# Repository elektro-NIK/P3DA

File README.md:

# P3DA

This is RGB controller based on Arduino board.

Features:
- 6 RGB chanels (18 mono-chanels)
- common anode or cathode
- light, effect, sound, external backlight modes
- white balance, gamma correction

Install:
- `pip3 install PyQt5` and `python3 setup.py install` for use in your system
- or `pip3 install -e .` for install all necessary modules

Using: 
- `./software/main.py` for starting
- `/software/test.py` test rainbow ilumination on 0 channel

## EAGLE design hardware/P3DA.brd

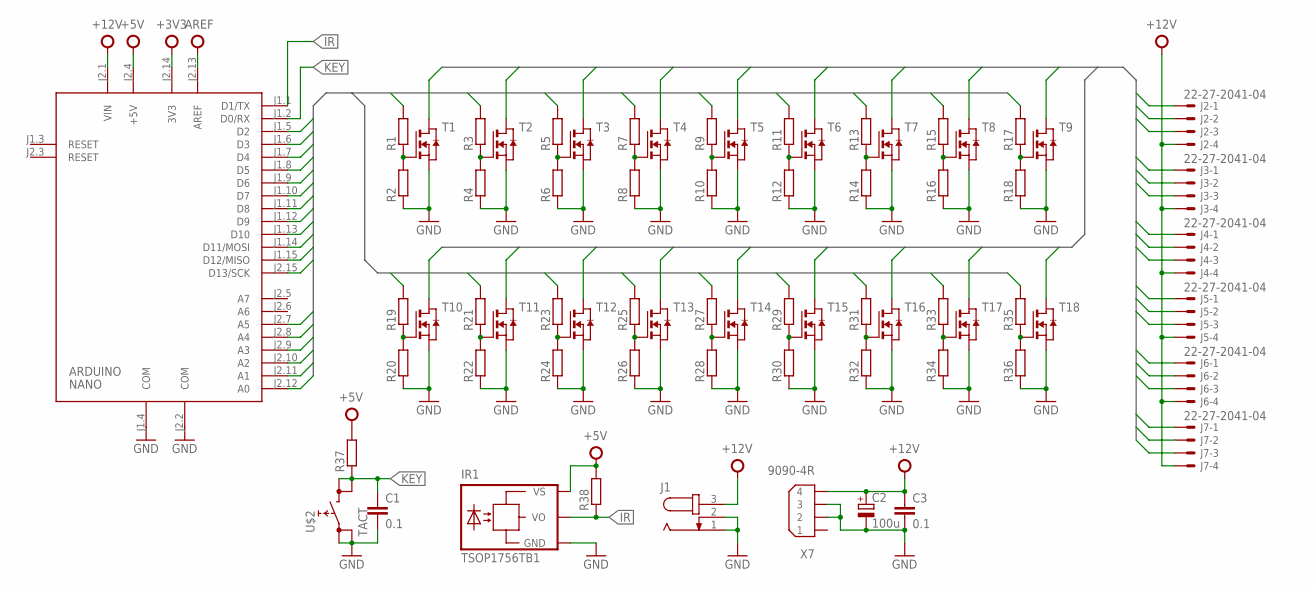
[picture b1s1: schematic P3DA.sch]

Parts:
ARDUINO: NANO; ARDUINO_NANO2
C1: 0.1; C0805
C2: 100u; E5-13
C3: 0.1; C1206
IR1: TSOP1756TB1; TSOP17_TB1
J1: JACK-PLUG1; SPC4078
J2, J3, J4, J5, J6, J7: 22-27-2041-04; 6410-04
R1, R2, R3, R4, R5, R6, R7, R8, R9, R10, R11, R12, R13, R14, R15, R16, R17, R18, R19, R20, R21, R22, R23, R24, R25, R26, R27, R28, R29, R30, R31, R32, R33, R34, R35, R36, R37, R38: R-EU_R0805; R0805
T1, T2, T3, T4, T5, T6, T7, T8, T9, T10, T11, T12, T13, T14, T15, T16, T17, T18: NMOSSOT23; SOT-23
U$2: TACT; TL1105
X7: 9090-4R

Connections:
+3V3: ARDUINO.J2.14 (3V3)
+5V: ARDUINO.J2.4 (+5V), IR1.VS, R37.2, R38.2
+12V: ARDUINO.J2.1 (VIN), C2.+, C3.1, J1.3, J2.4, J3.4, J4.4, J5.4, J6.4, J7.4, X7.4
AREF: ARDUINO.J2.13 (AREF)
B1: J2.1, T3.1 (D)
B2: J3.1, T6.1 (D)
B3: J4.1, T9.1 (D)
B4: J5.1, T12.1 (D)
B5: J6.1, T15.1 (D)
B6: J7.1, T18.1 (D)
B_IN1: ARDUINO.J1.5 (D2), R5.2
B_IN2: ARDUINO.J1.8 (D5), R11.2
B_IN3: ARDUINO.J1.11 (D8), R17.2
B_IN4: ARDUINO.J2.9 (A3), R23.2
B_IN5: ARDUINO.J2.12 (A0), R29.2
B_IN6: ARDUINO.J1.15 (D12/MISO), R35.2
G1: J2.3, T2.1 (D)
G2: J3.3, T5.1 (D)
G3: J4.3, T8.1 (D)
G4: J5.3, T11.1 (D)
G5: J6.3, T14.1 (D)
G6: J7.3, T17.1 (D)
GND: ARDUINO.J1.4 (COM), ARDUINO.J2.2 (COM), C1.2, C2.-, C3.2, IR1.GND, J1.1, J1.2, R2.1, R4.1, R6.1, R8.1, R10.1, R12.1, R14.1, R16.1, R18.1, R20.1, R22.1, R24.1, R26.1, R28.1, R30.1, R32.1, R34.1, R36.1, T1.2 (S), T2.2 (S), T3.2 (S), T4.2 (S), T5.2 (S), T6.2 (S), T7.2 (S), T8.2 (S), T9.2 (S), T10.2 (S), T11.2 (S), T12.2 (S), T13.2 (S), T14.2 (S), T15.2 (S), T16.2 (S), T17.2 (S), T18.2 (S), U$2.1 (0), U$2.3 (0), X7.2, X7.3
G_IN1: ARDUINO.J1.7 (D4), R3.2
G_IN2: ARDUINO.J1.10 (D7), R9.2
G_IN3: ARDUINO.J1.13 (D10), R15.2
G_IN4: ARDUINO.J2.7 (A5), R21.2
G_IN5: ARDUINO.J2.10 (A2), R27.2
G_IN6: ARDUINO.J2.15 (D13/SCK), R33.2
IR: ARDUINO.J1.1 (D1/TX), IR1.VO, R38.1
KEY: ARDUINO.J1.2 (D0/RX), C1.1, R37.1, U$2.2 (1), U$2.4 (1)
unnamed: R7.1, R8.2, T4.3 (G)
unnamed: R9.1, R10.2, T5.3 (G)
unnamed: R5.1, R6.2, T3.3 (G)
unnamed: R11.1, R12.2, T6.3 (G)
unnamed: R13.1, R14.2, T7.3 (G)
unnamed: R15.1, R16.2, T8.3 (G)
unnamed: R17.1, R18.2, T9.3 (G)
unnamed: R19.1, R20.2, T10.3 (G)
unnamed: R21.1, R22.2, T11.3 (G)
unnamed: R23.1, R24.2, T12.3 (G)
unnamed: R25.1, R26.2, T13.3 (G)
unnamed: R27.1, R28.2, T14.3 (G)
unnamed: R29.1, R30.2, T15.3 (G)
unnamed: R31.1, R32.2, T16.3 (G)
unnamed: R33.1, R34.2, T17.3 (G)
unnamed: R35.1, R36.2, T18.3 (G)
unnamed: R1.1, R2.2, T1.3 (G)
unnamed: R3.1, R4.2, T2.3 (G)
R1: J2.2, T1.1 (D)
R2: J3.2, T4.1 (D)
R3: J4.2, T7.1 (D)
R4: J5.2, T10.1 (D)
R5: J6.2, T13.1 (D)
R6: J7.2, T16.1 (D)
R_IN1: ARDUINO.J1.6 (D3), R1.2
R_IN2: ARDUINO.J1.9 (D6), R7.2
R_IN3: ARDUINO.J1.12 (D9), R13.2
R_IN4: ARDUINO.J2.8 (A4), R19.2
R_IN5: ARDUINO.J2.11 (A1), R25.2
R_IN6: ARDUINO.J1.14 (D11/MOSI), R31.2

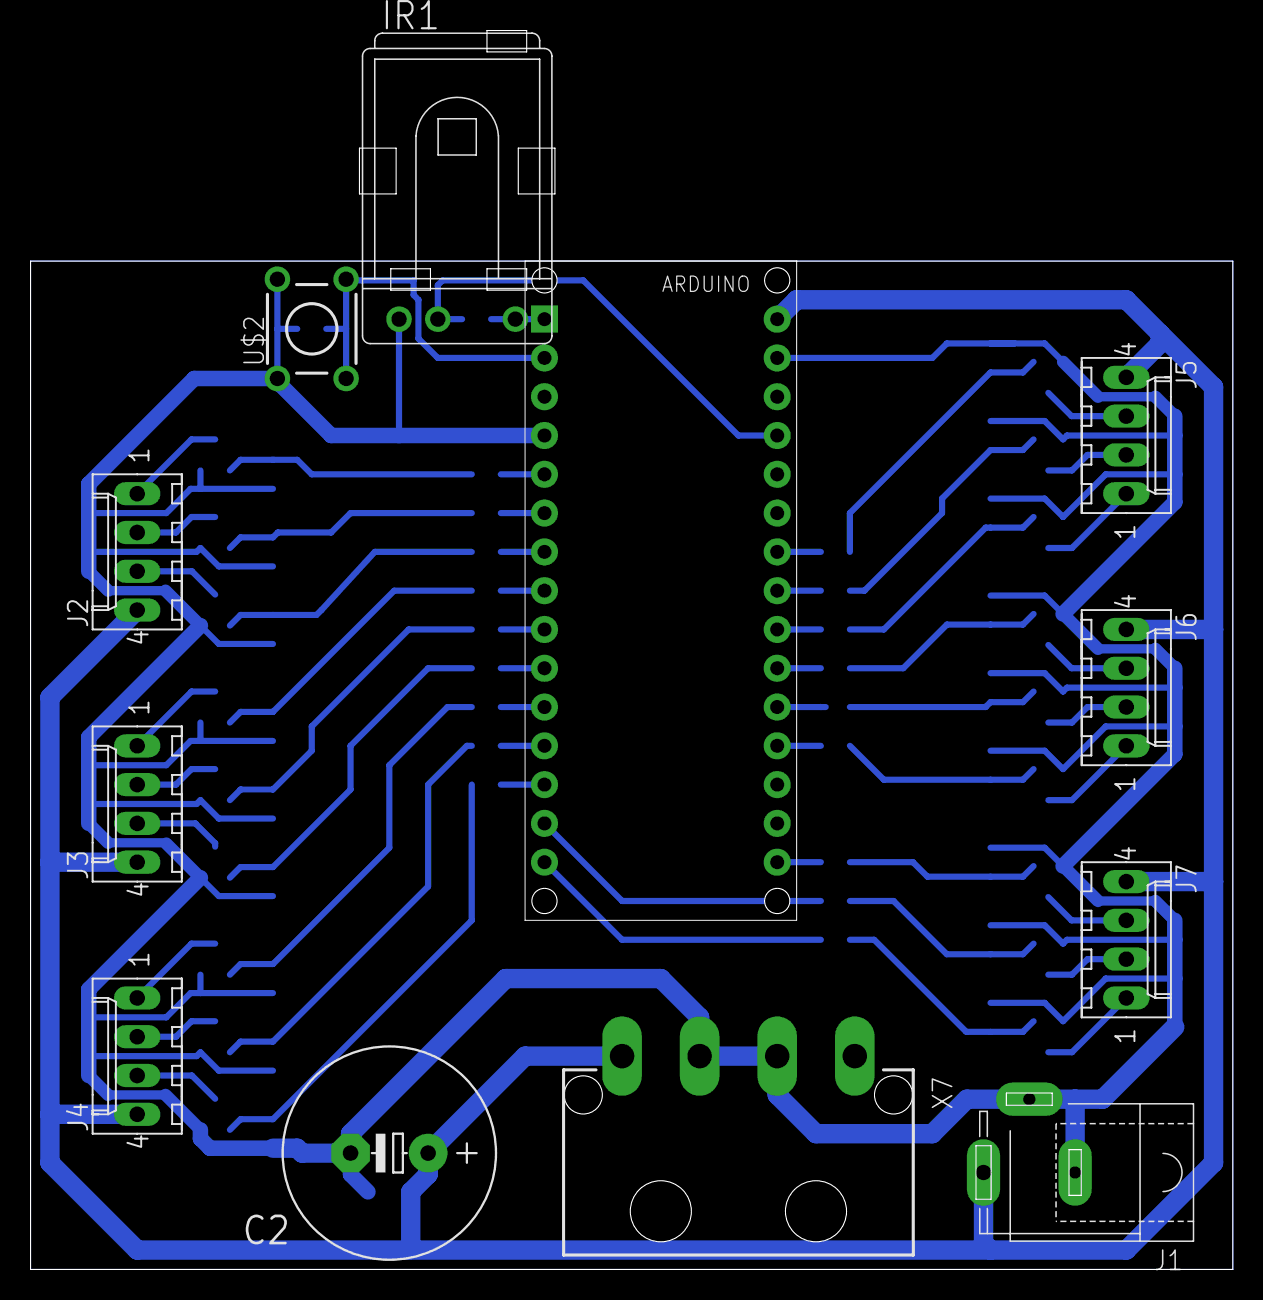
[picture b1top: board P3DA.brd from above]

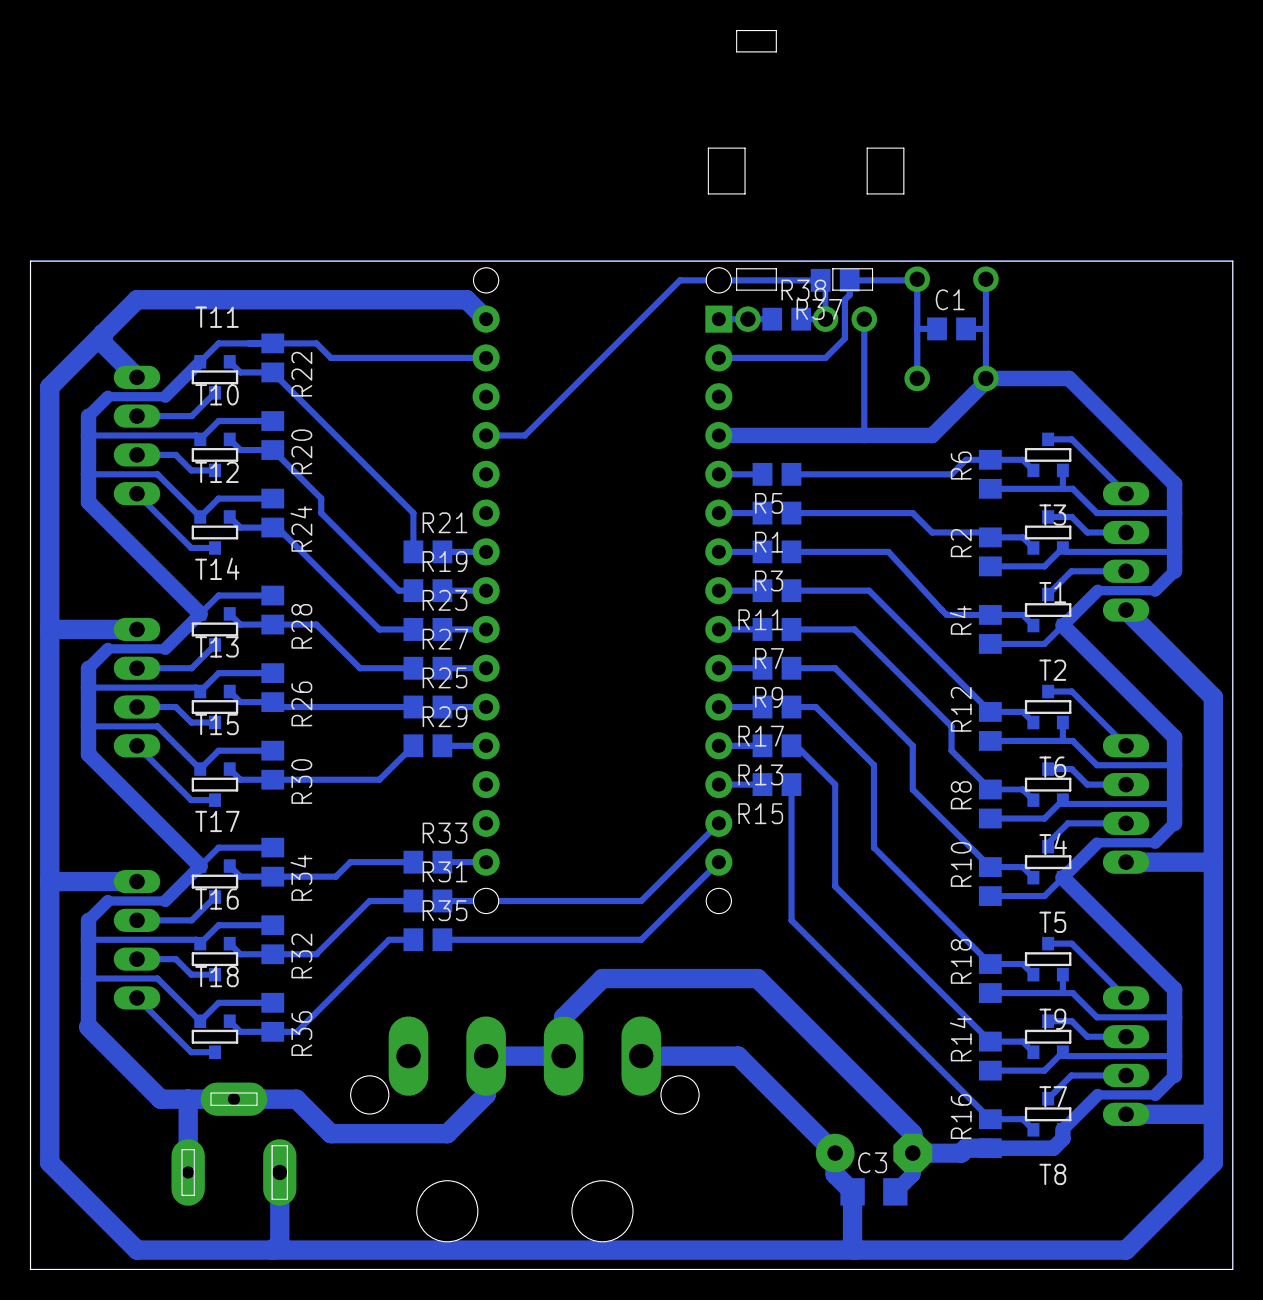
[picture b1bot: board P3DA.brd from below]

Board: 2 copper layers, 78.7 x 81.1 mm, 70 parts (58 on the bottom side), 59 nets.

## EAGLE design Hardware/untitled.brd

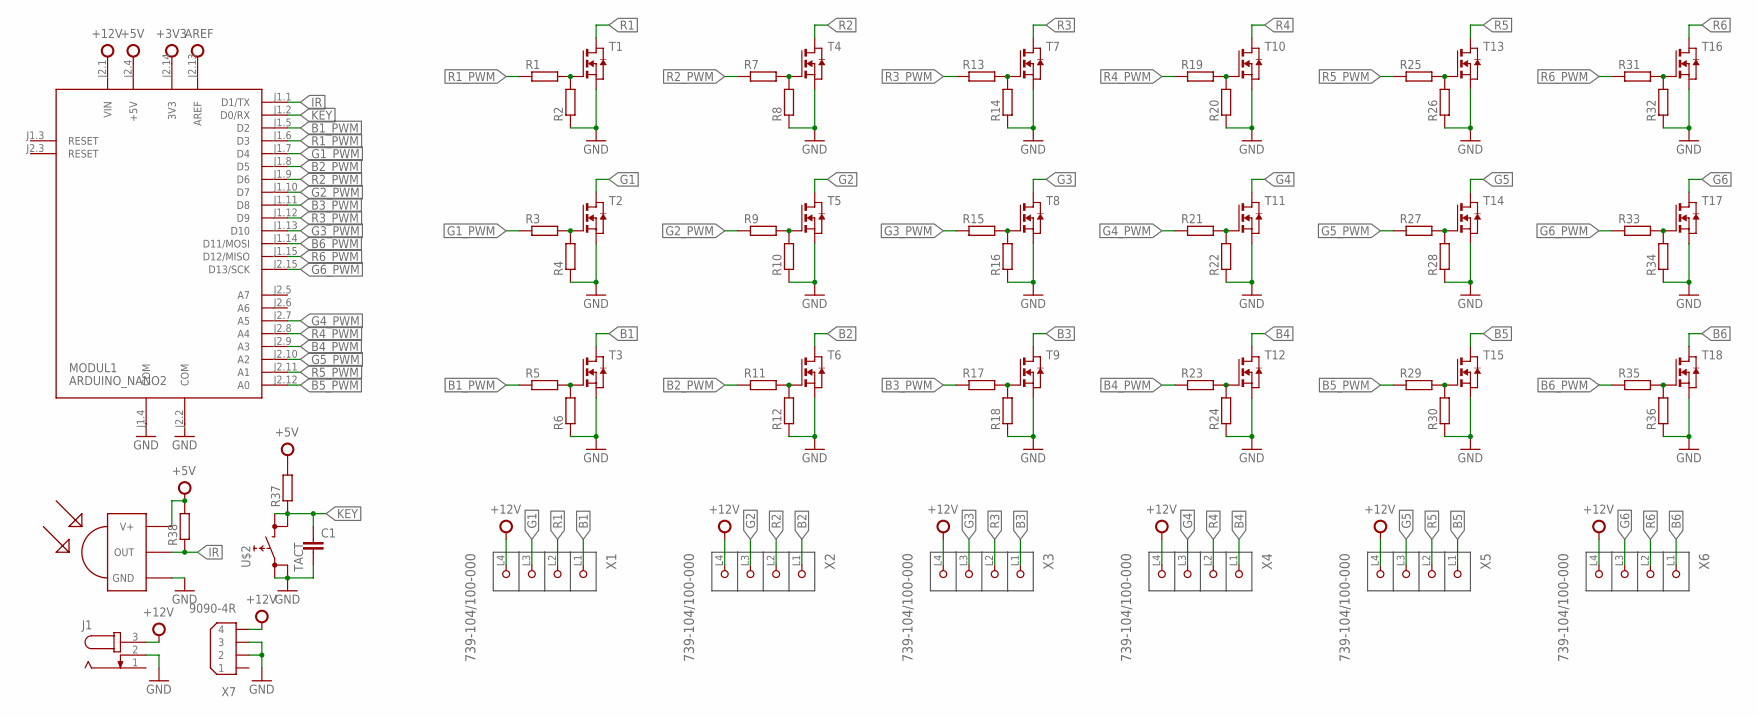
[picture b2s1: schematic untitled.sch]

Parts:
C1: C-EUC0805; C0805
J1: JACK-PLUG1; SPC4078
MODUL1: ARDUINO_NANO2
R1, R2, R3, R4, R5, R6, R7, R8, R9, R10, R11, R12, R13, R14, R15, R16, R17, R18, R19, R20, R21, R22, R23, R24, R25, R26, R27, R28, R29, R30, R31, R32, R33, R34, R35, R36, R37, R38: R-EU_R0805; R0805
T1, T2, T3, T4, T5, T6, T7, T8, T9, T10, T11, T12, T13, T14, T15, T16, T17, T18: NMOSSOT23; SOT-23
U$1: TSOP1738; TSOP17XX
U$2: TACT; TL1105
X1, X2, X3, X4, X5, X6: 739-104/100-000; P-739-104/100-000
X7: 9090-4R

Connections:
+3V3: MODUL1.J2.14 (3V3)
+5V: MODUL1.J2.4 (+5V), R37.2, R38.2, U$1.V+
+12V: J1.3, MODUL1.J2.1 (VIN), X1.L4 (P4), X2.L4 (P4), X3.L4 (P4), X4.L4 (P4), X5.L4 (P4), X6.L4 (P4), X7.4
AREF: MODUL1.J2.13 (AREF)
B1: T3.1 (D), X1.L1 (P1)
B1_PWM: MODUL1.J1.5 (D2), R5.1
B2: T6.1 (D), X2.L1 (P1)
B2_PWM: MODUL1.J1.8 (D5), R11.1
B3: T9.1 (D), X3.L1 (P1)
B3_PWM: MODUL1.J1.11 (D8), R17.1
B4: T12.1 (D), X4.L1 (P1)
B4_PWM: MODUL1.J2.9 (A3), R23.1
B5: T15.1 (D), X5.L1 (P1)
B5_PWM: MODUL1.J2.12 (A0), R29.1
B6: T18.1 (D), X6.L1 (P1)
B6_PWM: MODUL1.J1.14 (D11/MOSI), R35.1
G1: T2.1 (D), X1.L3 (P3)
G1_PWM: MODUL1.J1.7 (D4), R3.1
G2: T5.1 (D), X2.L3 (P3)
G2_PWM: MODUL1.J1.10 (D7), R9.1
G3: T8.1 (D), X3.L3 (P3)
G3_PWM: MODUL1.J1.13 (D10), R15.1
G4: T11.1 (D), X4.L3 (P3)
G4_PWM: MODUL1.J2.7 (A5), R21.1
G5: T14.1 (D), X5.L3 (P3)
G5_PWM: MODUL1.J2.10 (A2), R27.1
G6: T17.1 (D), X6.L3 (P3)
G6_PWM: MODUL1.J2.15 (D13/SCK), R33.1
GND: C1.2, J1.2, MODUL1.J1.4 (COM), MODUL1.J2.2 (COM), R2.1, R4.1, R6.1, R8.1, R10.1, R12.1, R14.1, R16.1, R18.1, R20.1, R22.1, R24.1, R26.1, R28.1, R30.1, R32.1, R34.1, R36.1, T1.2 (S), T2.2 (S), T3.2 (S), T4.2 (S), T5.2 (S), T6.2 (S), T7.2 (S), T8.2 (S), T9.2 (S), T10.2 (S), T11.2 (S), T12.2 (S), T13.2 (S), T14.2 (S), T15.2 (S), T16.2 (S), T17.2 (S), T18.2 (S), U$1.GND, U$2.1 (0), U$2.3 (0), X7.2, X7.3
IR: MODUL1.J1.1 (D1/TX), R38.1, U$1.OUT
KEY: C1.1, MODUL1.J1.2 (D0/RX), R37.1, U$2.2 (1), U$2.4 (1)
unnamed: R1.2, R2.2, T1.3 (G)
unnamed: R7.2, R8.2, T4.3 (G)
unnamed: R9.2, R10.2, T5.3 (G)
unnamed: R3.2, R4.2, T2.3 (G)
unnamed: R5.2, R6.2, T3.3 (G)
unnamed: R11.2, R12.2, T6.3 (G)
unnamed: R13.2, R14.2, T7.3 (G)
unnamed: R15.2, R16.2, T8.3 (G)
unnamed: R17.2, R18.2, T9.3 (G)
unnamed: R19.2, R20.2, T10.3 (G)
unnamed: R21.2, R22.2, T11.3 (G)
unnamed: R23.2, R24.2, T12.3 (G)
unnamed: R25.2, R26.2, T13.3 (G)
unnamed: R27.2, R28.2, T14.3 (G)
unnamed: R29.2, R30.2, T15.3 (G)
unnamed: R31.2, R32.2, T16.3 (G)
unnamed: R33.2, R34.2, T17.3 (G)
unnamed: R35.2, R36.2, T18.3 (G)
R1: T1.1 (D), X1.L2 (P2)
R1_PWM: MODUL1.J1.6 (D3), R1.1
R2: T4.1 (D), X2.L2 (P2)
R2_PWM: MODUL1.J1.9 (D6), R7.1
R3: T7.1 (D), X3.L2 (P2)
R3_PWM: MODUL1.J1.12 (D9), R13.1
R4: T10.1 (D), X4.L2 (P2)
R4_PWM: MODUL1.J2.8 (A4), R19.1
R5: T13.1 (D), X5.L2 (P2)
R5_PWM: MODUL1.J2.11 (A1), R25.1
R6: T16.1 (D), X6.L2 (P2)
R6_PWM: MODUL1.J1.15 (D12/MISO), R31.1

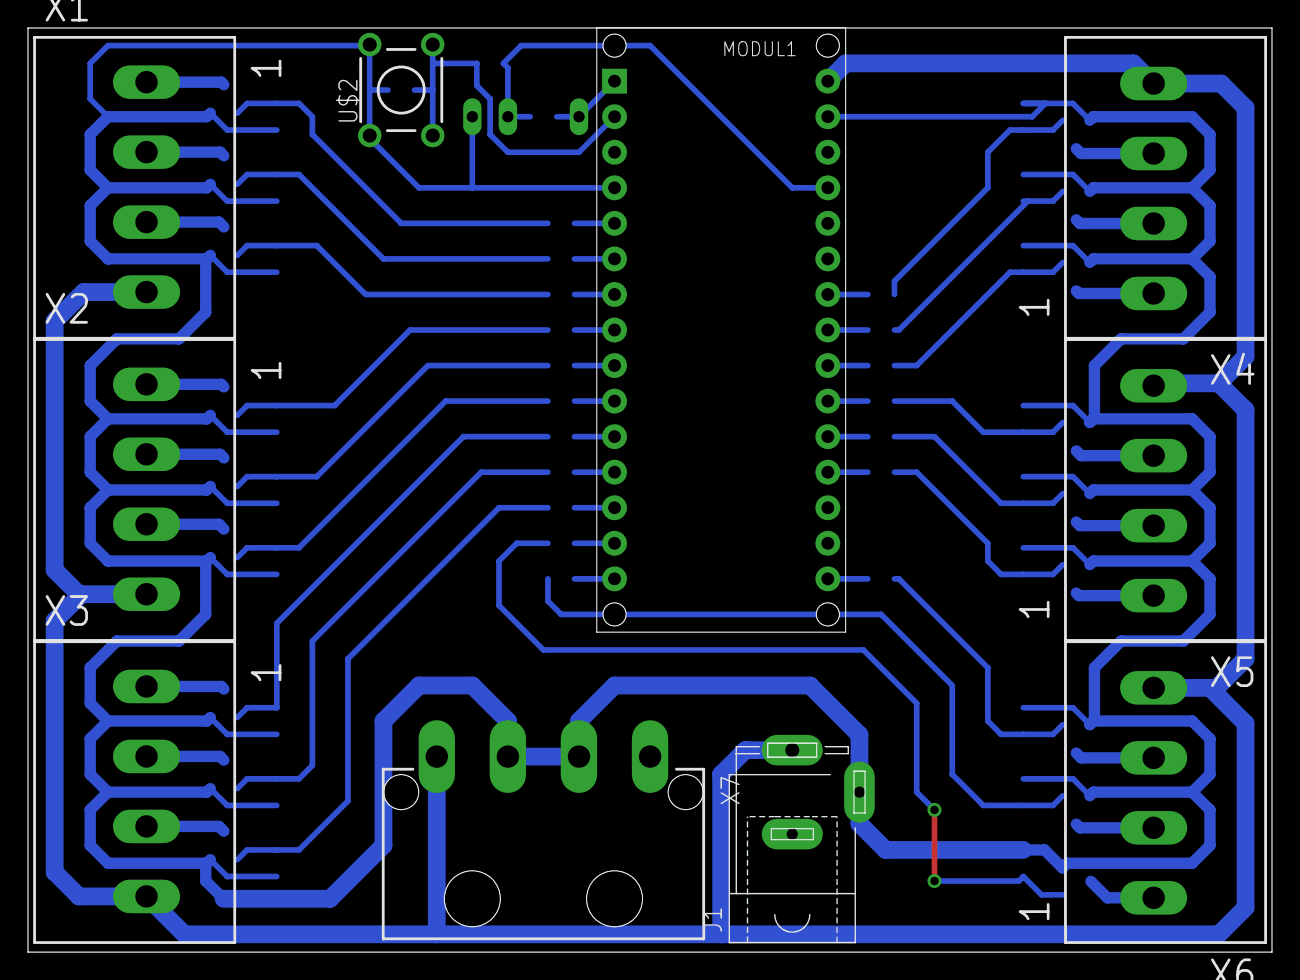
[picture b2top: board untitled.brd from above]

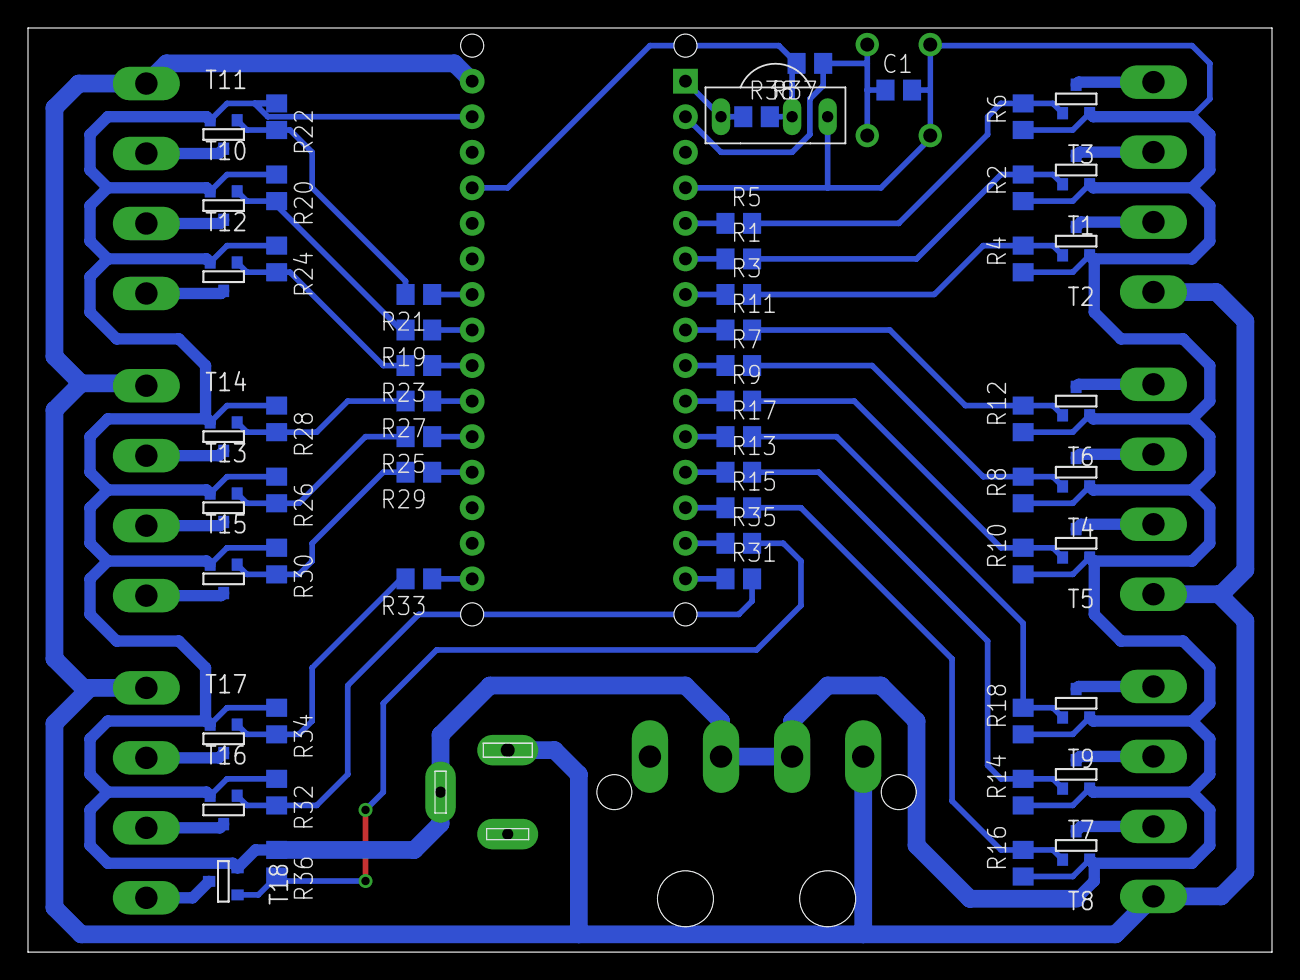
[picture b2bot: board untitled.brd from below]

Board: 2 copper layers, 88.9 x 66.0 mm, 68 parts (58 on the bottom side), 59 nets.

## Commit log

2016-09-03 Add hex-file, bugfix test.c
2016-09-03 Bugfix test.c
2016-09-03 Add Makefile
2016-09-03 Relocate all files
2016-09-04 Update all files
2016-09-04 Added Firmware directory
2016-09-04 Update: main.c. 0 level fixed. To fix: 255 level.
2016-09-05 Add choise common electrode in RGB module
2016-09-05 Orpho: CATODE -> CATHODE
2016-09-05 10bit PWM. Add avr-size in Makefile
2016-09-09 Add USART echo interface. TODO: 1:1 T0
2016-09-10 Added & fix USART interface. TODO: protocol
2016-12-16 Relocation all files
2016-12-16 Relocate all files.
2016-12-16 Fix location Firmware
2016-12-16 Fix location Firmware files
2017-02-03 Refactoring
2017-02-05 Add test.py
2017-02-06 Add gamma correction
2017-02-07 Add main.py for fast setting color
2017-02-10 Redesign 1st page GUI
2017-02-10 Redesign Ext. backlight page GUI
2017-02-10 Renaming GUI elements
2017-02-10 Move files to software
2017-02-11 Light page programming
2017-02-12 Fix multiple setting color
2017-02-12 Fix background color
2017-02-14 Main page sliders, palette and dial ok. TODO: colorchecker
2017-02-14 Added color selector
2017-02-14 Refactor
2017-02-15 Refactoring PCB and schematic
2017-02-16 Refactoring and bugfix
2017-02-16 Bugfix
2017-02-16 Relocate files
2017-02-16 TabIlumination update(), refactoring
2017-02-17 Refactoring and realization simple effects
2017-02-17 Finished Ilumination tab, added effects
2017-02-18 Getting raw audio data
2017-02-18 Added FFT
2017-02-19 Update form
2017-02-20 Sounds coding
2017-02-20 Add smooth audio effect
2017-02-21 Sound tab done. Bug fix, refactoring.
2017-02-21 Added setup functions without gamma graphic.
2017-02-21 It's bad idea
2017-02-22 Setup tab done, added icon, update form
2017-02-22 Added pyqtgraph
2017-02-22 Fix mid slider value
2017-02-22 Started ext. backlight tab
2017-02-23 Realized setting zone of the external backlight
2017-02-23 Bugfix: high frequency spinbox value
2017-02-24 Little fix
2017-02-27 Add resizable rects
2017-02-28 Added ext. backlight outputing
2017-02-28 Fixed form, bugfix
2017-03-01 Updated form
2017-03-02 Fixed resizing bug
2017-03-03 Add UML
2017-03-04 Add save & restore methods
2017-03-04 Add border
2017-03-05 Added last color selector shift, saving and restoring 2 tabs
2017-03-06 Added saving all tabs without Ext backlight
2017-03-07 Refactored savesettings()
2017-03-08 Refactored restoresettings()
2017-03-09 Update ext. backlight tab
2017-03-10 Added saving and restoring external backlight tab
2017-03-14 Updated UML
2017-03-16 Added splash screen
2017-03-17 Add localization files
2017-03-18 Setting for latest board
2017-03-18 Bugfix: lighting
2017-03-18 Update for latest board
2017-03-18 Bugfix: don't update colors on restored palette
2017-03-20 Added setup.py
2017-03-21 Bugfix: freezing on sound effects
2017-03-22 ATmega328 -> ATmega168
